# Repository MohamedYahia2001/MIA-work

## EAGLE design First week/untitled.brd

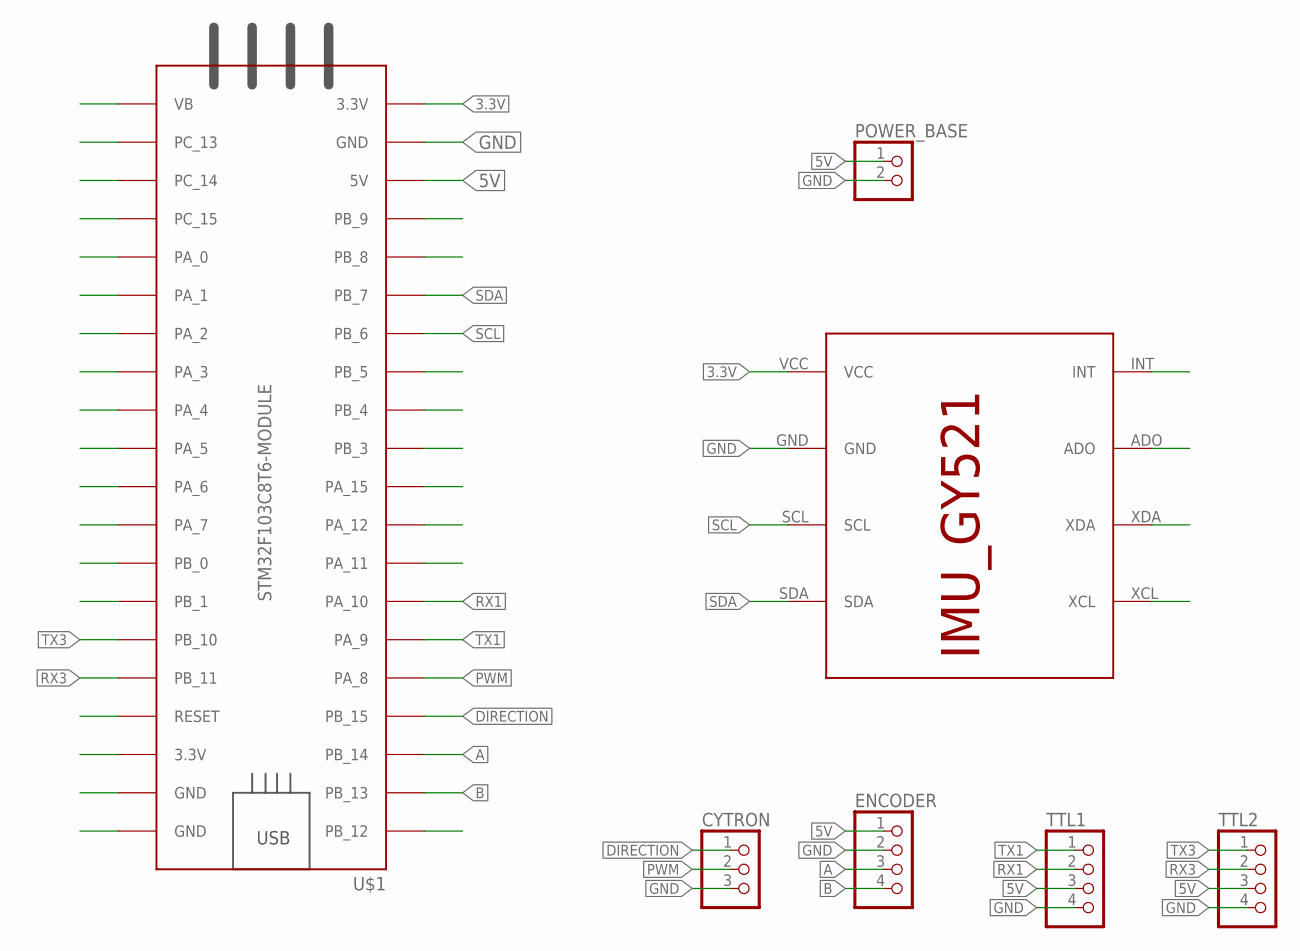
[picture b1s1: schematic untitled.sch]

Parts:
CYTRON: PINHD-1X3; 1X03
ENCODER: PINHD-1X4; 1X04
POWER_BASE: PINHD-2_DATA; 1X02_DATA
TTL1, TTL2: PINHD-1X4; 1X04
U$1: STM32F103C8T6-MODULE
U$2: IMU_ROBOCON_GY521; IMU_GY521

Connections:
3.3V: U$1.3.3V_1 (3.3V), U$1.3.3V_2 (3.3V), U$2.VCC
5V: ENCODER.1, POWER_BASE.1, TTL1.3, TTL2.3, U$1.5V
A: ENCODER.3, U$1.PB_14
B: ENCODER.4, U$1.PB_13
DIRECTION: CYTRON.1, U$1.PB_15
GND: CYTRON.3, ENCODER.2, POWER_BASE.2, TTL1.4, TTL2.4, U$1.GND_1 (GND), U$1.GND_2 (GND), U$1.GND_3 (GND), U$2.GND
PWM: CYTRON.2, U$1.PA_8
QWRGF3A: U$1.PB_1
RX1: TTL1.2, U$1.PA_10
RX3: TTL2.2, U$1.PB_11
SCL: U$1.PB_6, U$2.SCL
SDA: U$1.PB_7, U$2.SDA
TX1: TTL1.1, U$1.PA_9
TX3: TTL2.1, U$1.PB_10
WAF: U$1.PB_0

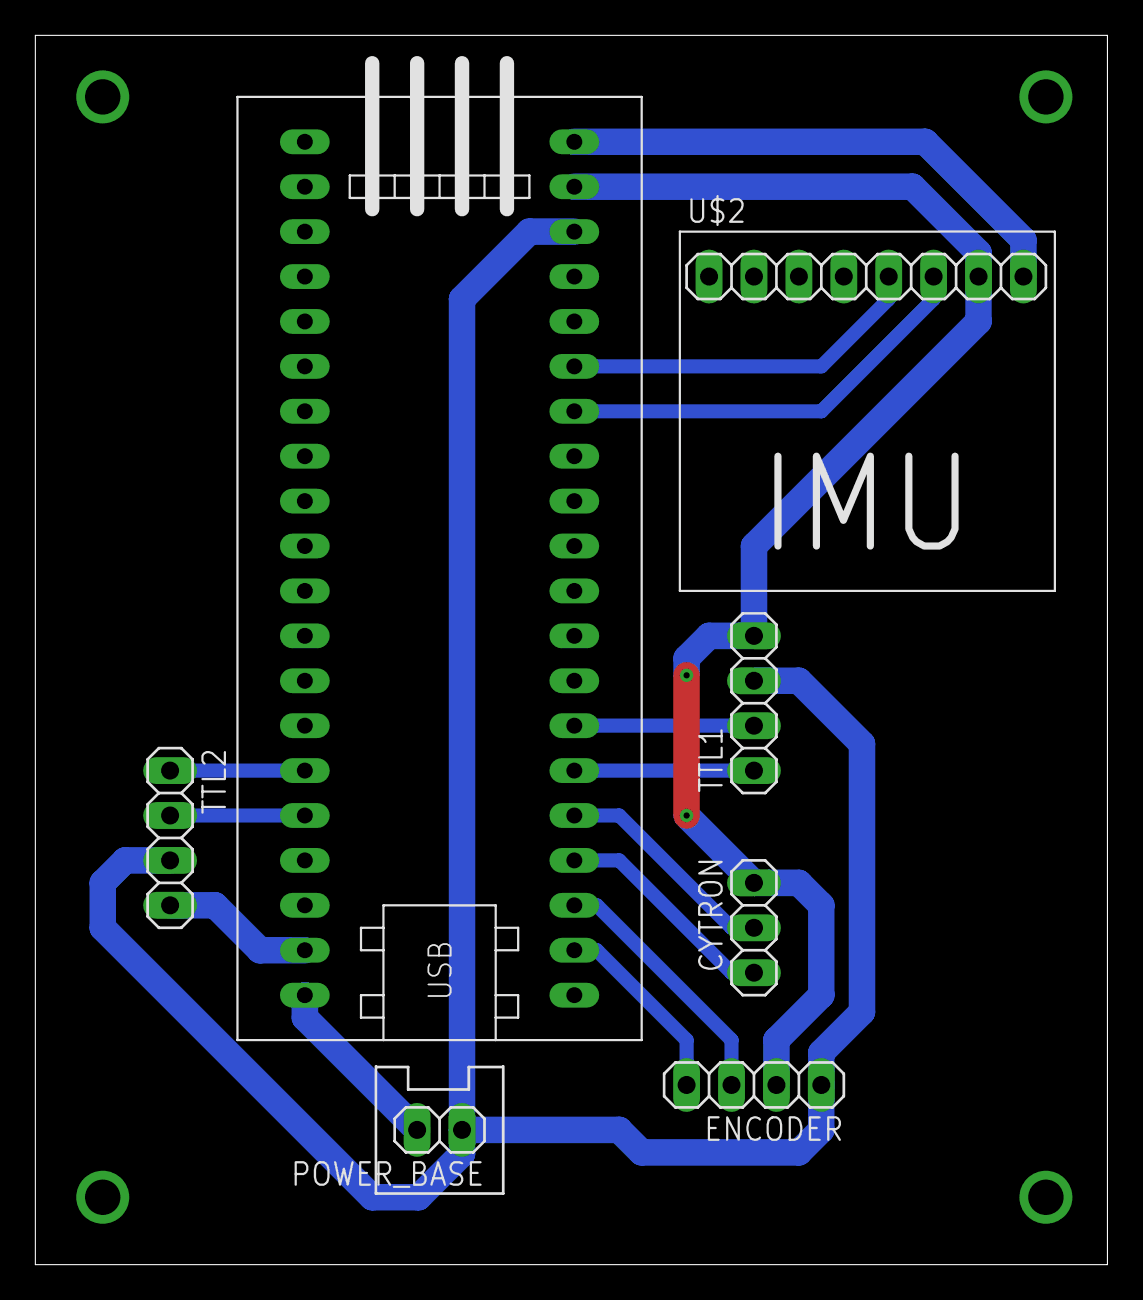
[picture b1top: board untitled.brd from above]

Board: 2 copper layers, 60.6 x 69.5 mm, 7 parts (0 on the bottom side), 13 nets.

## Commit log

2021-10-28 edit1
2021-10-28 Create Second week
2021-10-29 change
